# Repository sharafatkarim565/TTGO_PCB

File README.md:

# TTGO_PCB
TECHTONICS TTGO T-Call v1.3 ESP32 Wireless Communication Module for Arduino | SIM800L GPRS Module (with Antenna)

#TOP VIEW

#BOTTOM VIEW

https://github.com/sharafatkarim565/TTGO_PCB/assets/169882984/35da6a52-983e-43cd-ab66-9002d637396b

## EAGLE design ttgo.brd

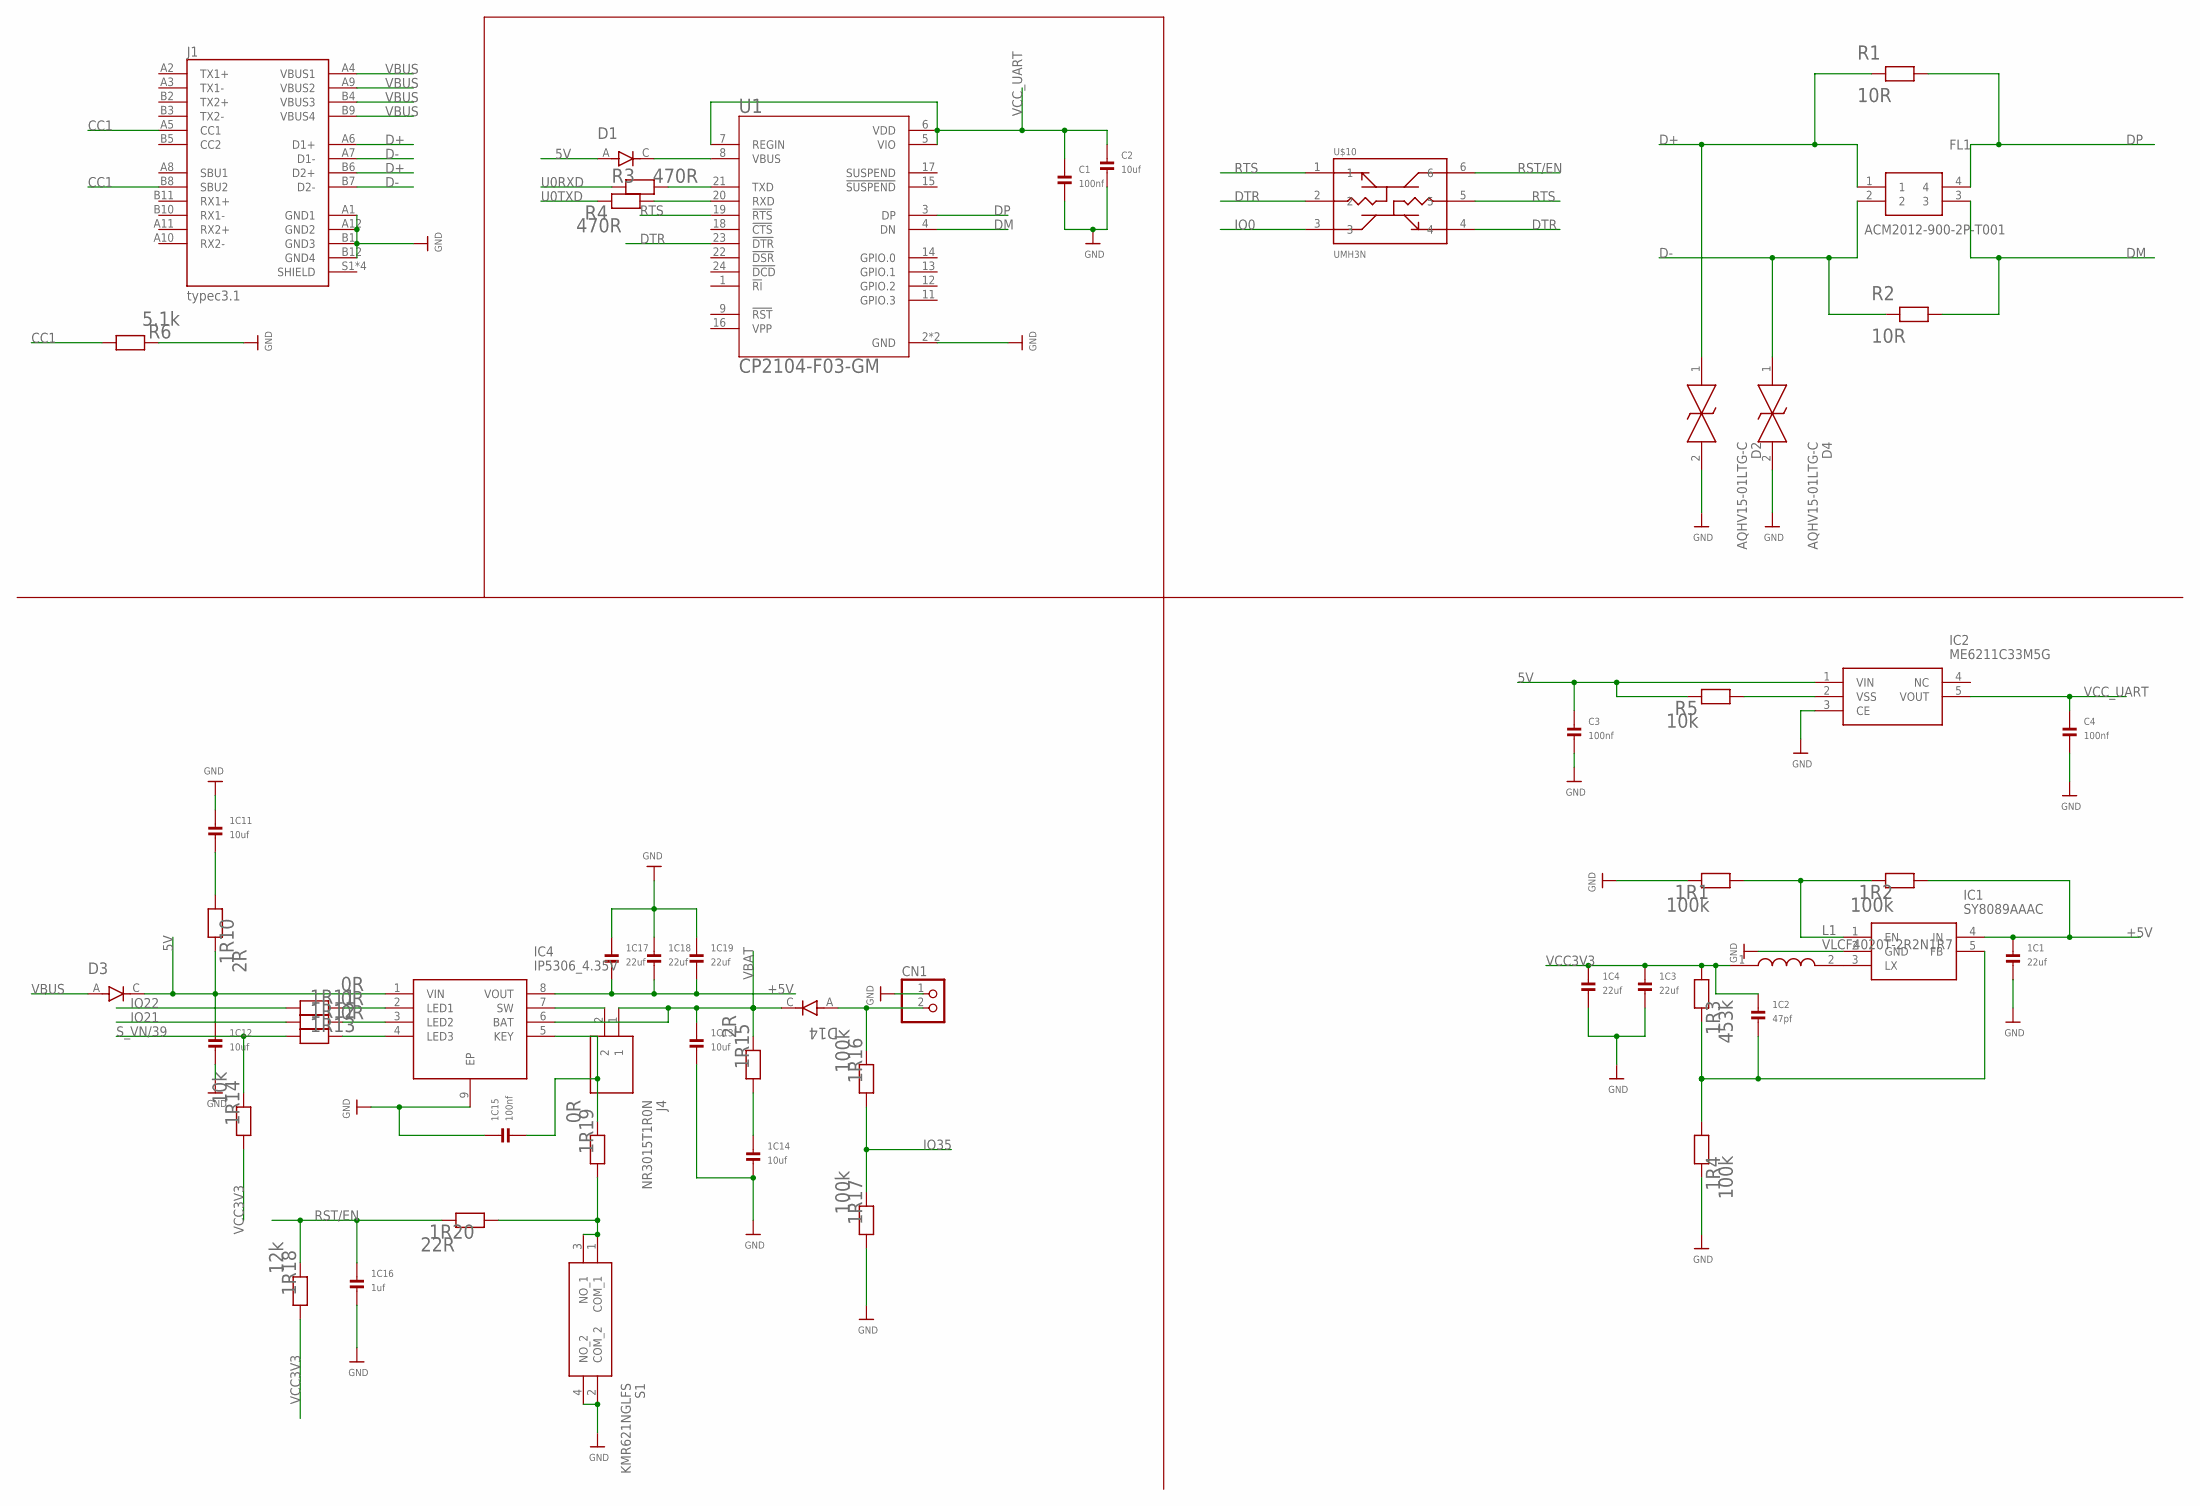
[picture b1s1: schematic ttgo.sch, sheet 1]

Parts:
1C1, 1C3, 1C4, 1C17, 1C18, 1C19: 22uf; _0402
1C2: 47pf; _0402
1C11, 1C12, 1C13, 1C14: 10uf; _0402
1C15: 100nf; _0402
1C16: 1uf; _0402
1R1, 1R2, 1R4, 1R16, 1R17: 100k; 0402
1R3: 453k; 0402
1R10, 1R15: 2R; 0402
1R11, 1R12, 1R13, 1R19: 0R; 0402
1R14: 10k; 0402
1R18: 12k; 0402
1R20: 22R; 0402
C1, C3, C4: 100nf; _0402
C2: 10uf; _0402
CN1: JST_2PINSH2; JSTSH2
D1, D3, D14: 1N4148WT; SODFL1608X70N
D2, D4: AQHV15-01LTG-C; AQHV1501LTGC
FL1: ACM2012-900-2P-T001; ACM20129002PT001
IC1: SY8089AAAC; SOT95P285X140-5N
IC2: ME6211C33M5G; SOT95P282X145-5N
IC4: IP5306_4.35V; SOIC127P600X165-9N
J1: typec3.1; MOLEX_105450-0101
J4: NR3015T1R0N
L1: VLCF4020T-2R2N1R7; VLCF4020_1
R1, R2: 10R; 0402
R3, R4: 470R; 0402
R5: 10k; 0402
R6: 5.1k; 0402
S1: KMR621NGLFS
U1: CP2104-F03-GM; QFN50P400X400X80-25N
U$10: UMH3N; SOP65P210X100-6N

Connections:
5V: 1C12.1, 1R10.1, C3.1, D1.A, D3.C, IC2.1 (VIN), IC4.1 (VIN), R5.1
+5V: 1C1.1, 1C17.2, 1C18.2, 1C19.2, 1R2.2, IC1.4 (IN), IC4.8 (VOUT); also elsewhere on the board
CC1: J1.A5 (CC1), J1.B8 (SBU2), R6.2
D+: D2.1, FL1.1, J1.A6 (D1+), J1.B6 (D2+), R1.1
D-: D4.1, FL1.2, J1.A7 (D1-), J1.B7 (D2-), R2.1
DM: FL1.3, R2.2, U1.4 (DN)
DP: FL1.4, R1.2, U1.3 (DP)
DTR: U1.23 (!DTR), U$10.2, U$10.4
GND: 1C1.2, 1C3.2, 1C4.2, 1C11.1, 1C12.2, 1C13.2, 1C14.2, 1C15.1, 1C16.2, 1C17.1, 1C18.1, 1C19.1, 1R1.1, 1R4.1, 1R17.2, C1.2, C2.2, C3.2, C4.2, CN1.1, D2.2, D4.2, IC1.2 (GND), IC2.3 (CE), IC4.9 (EP), J1.A1 (GND1), J1.A12 (GND2), J1.B1 (GND3), J1.B12 (GND4), R6.1, S1.2 (COM_2), S1.4 (NO_2), U1.2 (GND), U1.25 (GND); also elsewhere on the board
IO0: U$10.3; also elsewhere on the board
IO21: 1R12.2; also elsewhere on the board
IO22: 1R11.2; also elsewhere on the board
IO35: 1R16.2, 1R17.1; also elsewhere on the board
unnamed: D1.C, U1.8 (VBUS)
unnamed: R3.2, U1.21 (TXD)
unnamed: R4.2, U1.20 (RXD)
unnamed: IC2.2 (VSS), R5.2
unnamed: 1R1.2, 1R2.1, IC1.1 (EN)
unnamed: IC1.3 (LX), L1.2
unnamed: 1C2.2, 1R3.1, 1R4.2, IC1.5 (FB)
unnamed: 1C14.1, 1R15.2
unnamed: 1C11.2, 1R10.2
unnamed: 1R11.1, IC4.2 (LED1)
unnamed: 1C15.2, 1R19.1, IC4.5 (KEY)
unnamed: 1R12.1, IC4.3 (LED2)
unnamed: 1R16.1, CN1.2, D14.A
unnamed: 1R13.1, IC4.4 (LED3)
unnamed: IC4.7 (SW), J4.2
unnamed: 1R19.2, 1R20.2, S1.1 (COM_1), S1.3 (NO_1)
RST/EN: 1C16.1, 1R18.1, 1R20.1, U$10.6; also elsewhere on the board
RTS: U1.19 (!RTS), U$10.1, U$10.5
S_VN/39: 1R13.2, 1R14.1; also elsewhere on the board
U0RXD: R3.1; also elsewhere on the board
U0TXD: R4.1; also elsewhere on the board
VBAT: 1C13.1, 1R15.1, D14.C, IC4.6 (BAT), J4.1
VBUS: D3.A, J1.A4 (VBUS1), J1.A9 (VBUS2), J1.B4 (VBUS3), J1.B9 (VBUS4)
VCC3V3: 1C2.1, 1C3.1, 1C4.1, 1R3.2, 1R14.2, 1R18.2, L1.1; also elsewhere on the board
VCC_UART: C1.1, C2.1, C4.1, IC2.5 (VOUT), U1.5 (VIO), U1.6 (VDD), U1.7 (REGIN)

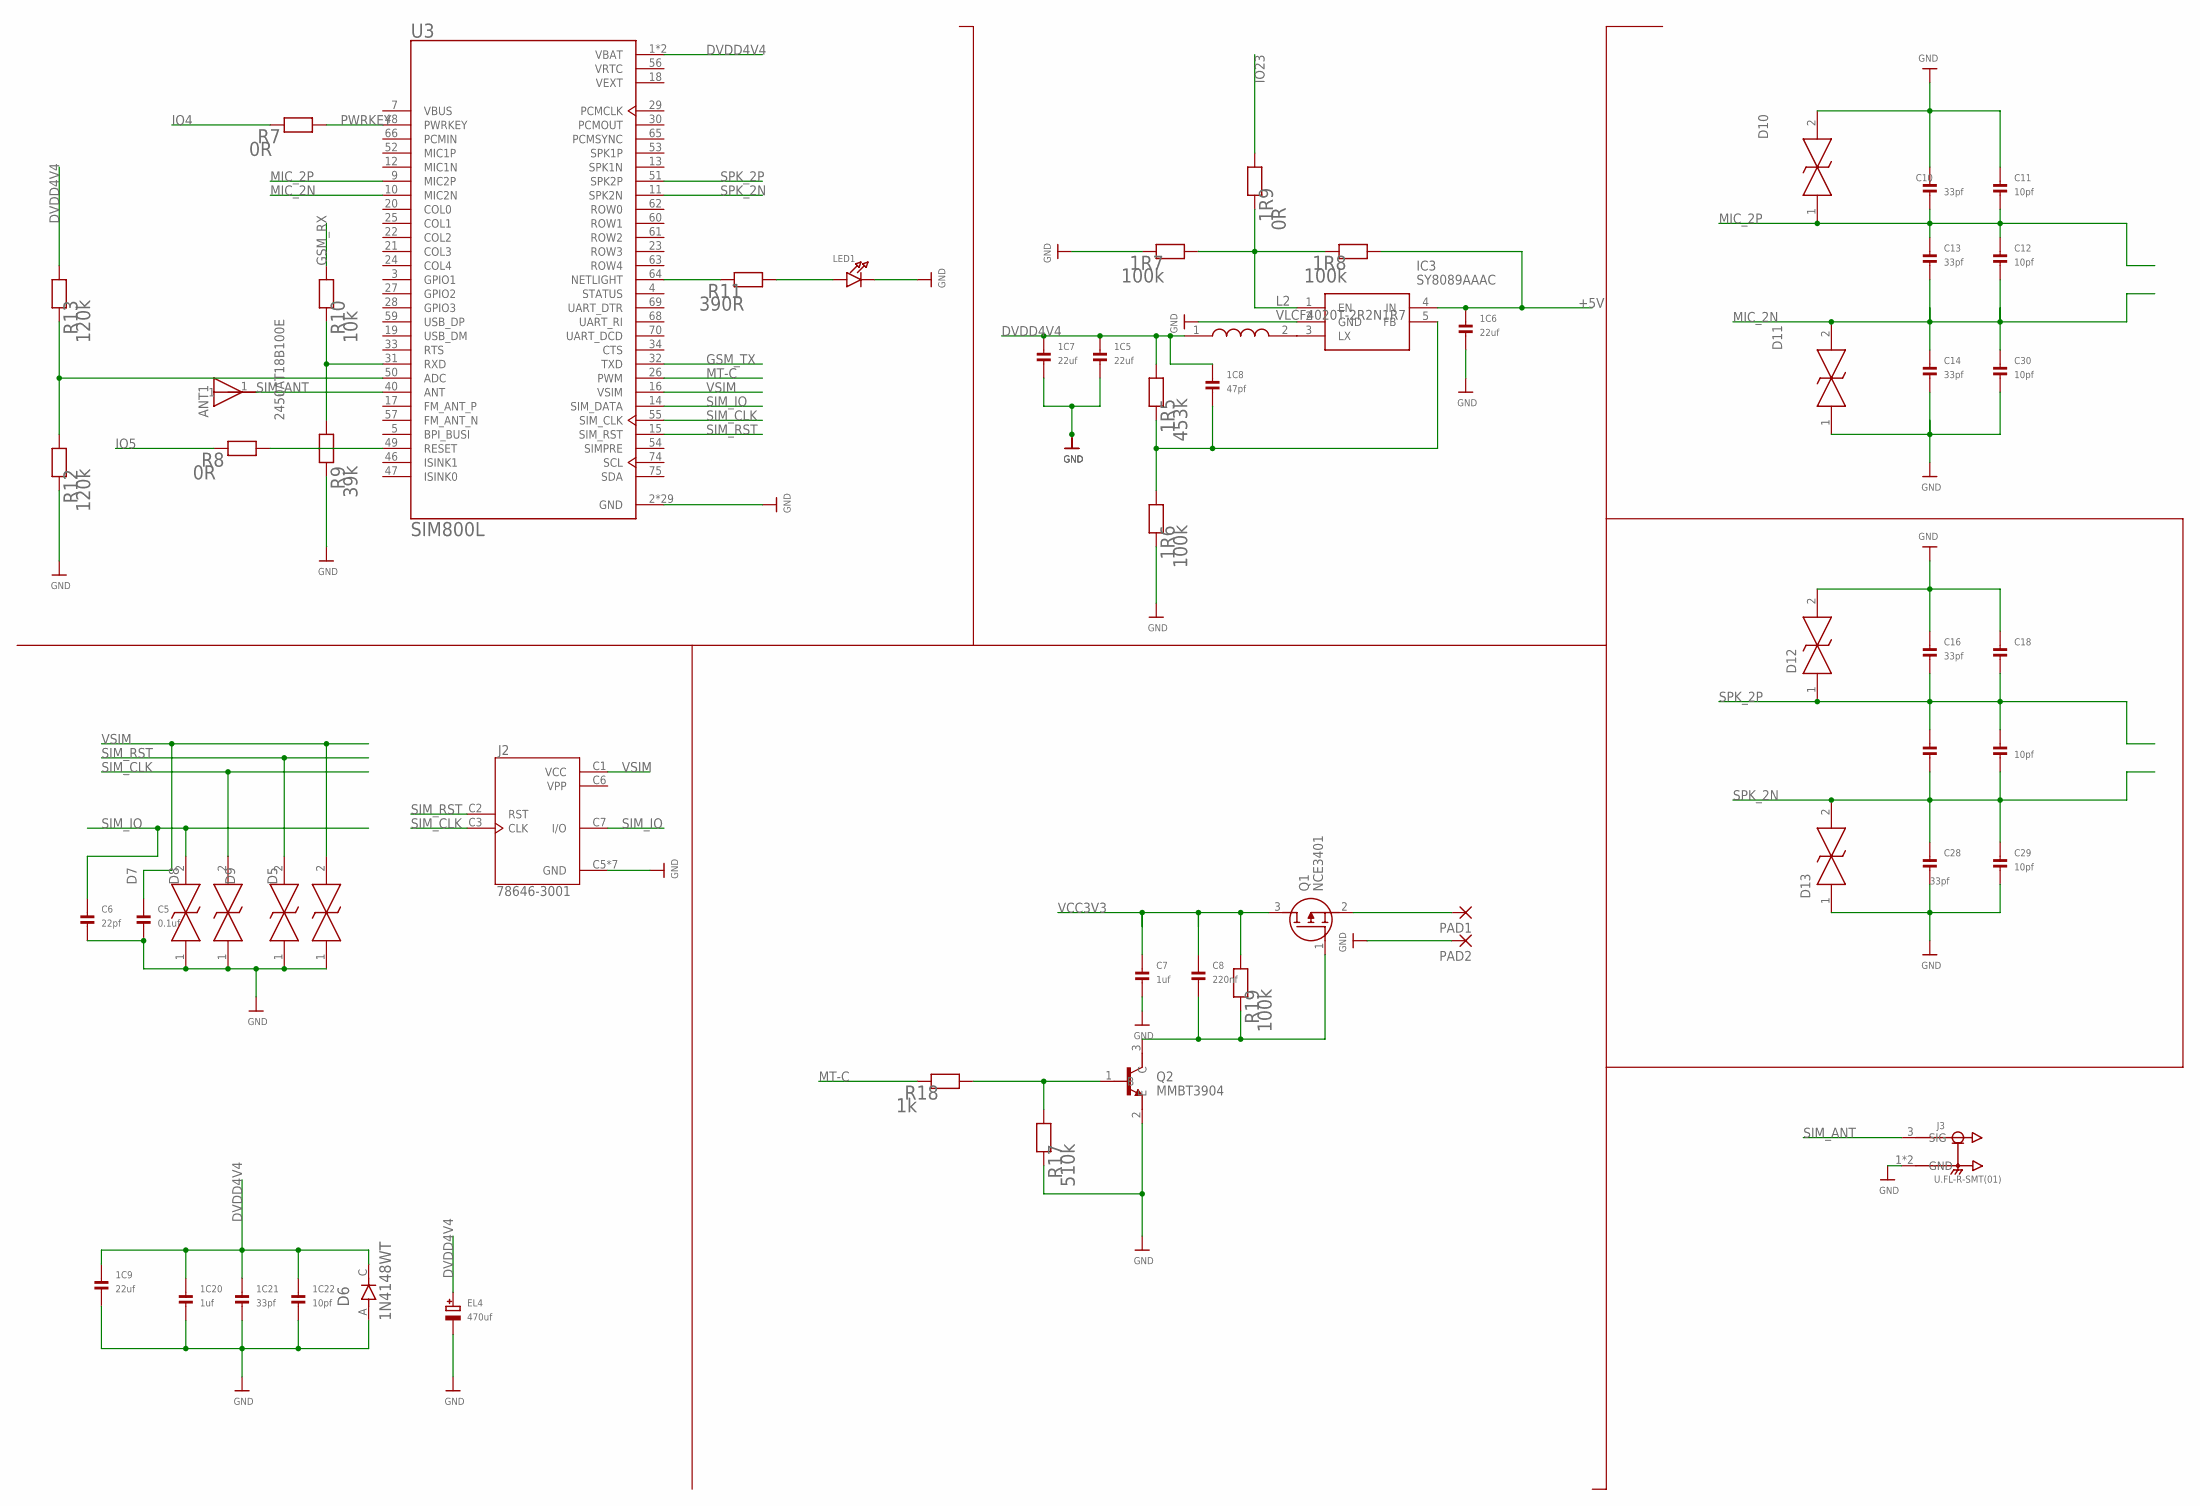
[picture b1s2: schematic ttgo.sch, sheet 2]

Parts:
1C5, 1C6, 1C7, 1C9: 22uf; _0402
1C8: 47pf; _0402
1C20: 1uf; _0402
1C21: 33pf; _0402
1C22: 10pf; _0402
1R5: 453k; 0402
1R6, 1R7, 1R8: 100k; 0402
1R9: 0R; 0402
ANT1: 2450AT18B100E; ANT_2450AT18B100E
C5: 0.1uf; _0402
C6: 22pf; _0402
C7: 1uf; _0402
C8: 220nf; _0402
C10, C13, C14, C16, C26, C28: 33pf; _0402
C11, C12, C18, C20, C29, C30: 10pf; _0402
D5, D7, D8, D9, D10, D11, D12, D13: AQHV15-01LTG-C; AQHV1501LTGC
D6: 1N4148WT; SODFL1608X70N
EL4: 470uf; EIA6032-28/C-R
IC3: SY8089AAAC; SOT95P285X140-5N
J2: 78646-3001; MOLEX_78646-3001
J3: U.FL-R-SMT(01); HRS_U.FL-R-SMT(01)
L2: VLCF4020T-2R2N1R7; VLCF4020_1
LED1: LED0603_NOOUTLINE; CHIPLED_0603_NOOUTLINE
PAD1, PAD2: SMD2; SMD1,27-2,54
Q1: NCE3401; SOT95P240X115-3N
Q2: MMBT3904; SOT95P240X120-3N
R7, R8: 0R; 0402
R9: 39k; 0402
R10: 10k; 0402
R11: 390R; 0402
R12, R13: 120k; 0402
R17: 510k; 0402
R18: 1k; 0402
R19: 100k; 0402
U3: SIM800L; MODULE_SIM800L

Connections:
+5V: 1C6.1, 1R8.2, IC3.4 (IN); also elsewhere on the board
DVDD4V4: 1C5.1, 1C7.1, 1C8.1, 1C9.1, 1C20.1, 1C21.1, 1C22.1, 1R5.2, D6.C, EL4.+, L2.1, R13.2, U3.1 (VBAT), U3.42 (VBAT)
GND: 1C5.2, 1C6.2, 1C7.2, 1C9.2, 1C20.2, 1C21.2, 1C22.2, 1R6.1, 1R7.1, C5.2, C6.2, C7.2, C10.1, C11.1, C14.2, C16.1, C18.1, C28.2, C29.2, C30.2, D5.1, D6.A, D7.1, D8.1, D9.1, D10.2, D11.1, D12.2, D13.1, EL4.-, IC3.2 (GND), J2.C5 (GND), J2.G1 (GND), J2.G2 (GND), J2.G3 (GND), J2.G4 (GND), J2.G5 (GND), J2.G6 (GND), J3.1 (GND), J3.2 (GND), LED1.C, PAD2.1, Q2.2 (E), R9.1, R12.1, R17.1, U3.2 (GND), U3.6 (GND), U3.8 (GND), U3.35 (GND), U3.37 (GND), U3.38 (GND), U3.39 (GND), U3.41 (GND), U3.43 (GND), U3.44 (GND), U3.45 (GND), U3.58 (GND), U3.67 (GND), U3.71 (GND), U3.72 (GND), U3.73 (GND), U3.76 (GND), U3.77 (GND), U3.78 (GND), U3.79 (GND), U3.80 (GND), U3.81 (GND), U3.82 (GND), U3.83 (GND), U3.84 (GND), U3.85 (GND), U3.86 (GND), U3.87 (GND), U3.88 (GND); also elsewhere on the board
GSM_RX: R10.2; also elsewhere on the board
GSM_TX: U3.32 (TXD); also elsewhere on the board
IO4: R7.1; also elsewhere on the board
IO5: R8.1; also elsewhere on the board
IO23: 1R9.2; also elsewhere on the board
MIC_2N: C12.2, C13.2, C14.1, C30.1, D11.2, U3.10 (MIC2N); also elsewhere on the board
MIC_2P: C10.2, C11.2, C12.1, C13.1, D10.1, U3.9 (MIC2P); also elsewhere on the board
MT-C: R18.1, U3.26 (PWM)
unnamed: 1R7.2, 1R8.1, 1R9.1, IC3.1 (EN)
unnamed: R12.2, R13.1, U3.50 (ADC)
unnamed: IC3.3 (LX), L2.2
unnamed: R11.1, U3.64 (NETLIGHT)
unnamed: 1C8.2, 1R5.1, 1R6.2, IC3.5 (FB)
unnamed: Q2.1 (B), R17.2, R18.2
unnamed: PAD1.1, Q1.2 (S)
unnamed: R9.2, R10.1, U3.31 (RXD)
unnamed: R8.2, U3.49 (RESET)
unnamed: C8.2, Q1.1 (G), Q2.3 (C), R19.1
unnamed: LED1.A, R11.2
PWRKEY: R7.2, U3.48 (PWRKEY)
SIM_ANT: ANT1.1, J3.3 (SIG), U3.40 (ANT)
SIM_CLK: D8.2, J2.C3 (CLK), U3.55 (SIM_CLK)
SIM_IO: C6.1, D7.2, J2.C7 (I/O), U3.14 (SIM_DATA)
SIM_RST: D9.2, J2.C2 (RST), U3.15 (SIM_RST)
SPK_2N: C20.2, C26.2, C28.1, C29.1, D13.2, U3.11 (SPK2N); also elsewhere on the board
SPK_2P: C16.2, C18.2, C20.1, C26.1, D12.1, U3.51 (SPK2P); also elsewhere on the board
VCC3V3: C7.1, C8.1, Q1.3 (D), R19.2; also elsewhere on the board
VEXT: U3.18 (VEXT)
VPP: J2.C6 (VPP)
VRTC: U3.56 (VRTC)
VSIM: C5.1, D5.2, J2.C1 (VCC), U3.16 (VSIM)

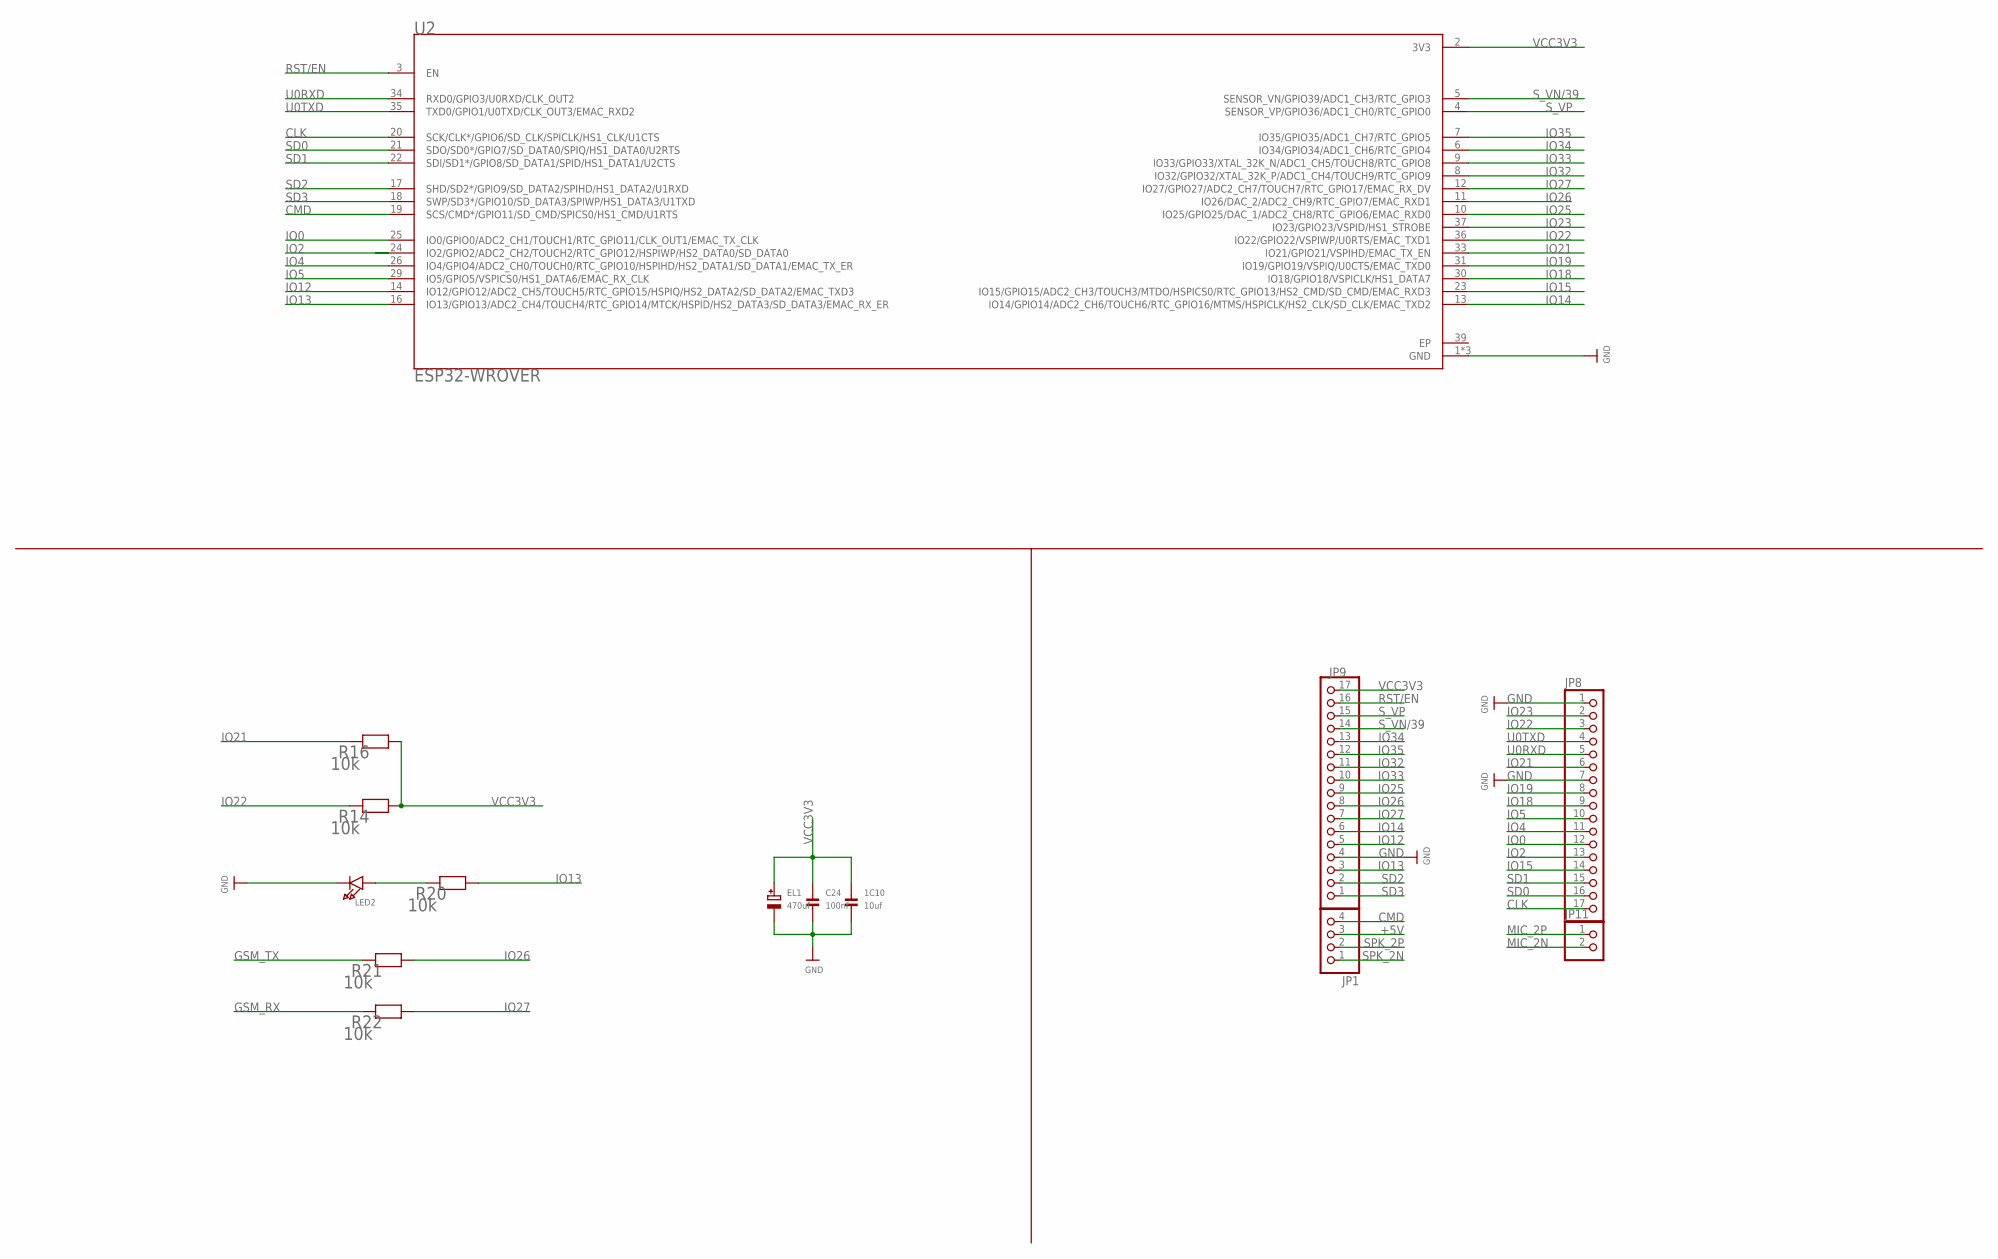
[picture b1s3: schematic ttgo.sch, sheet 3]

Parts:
1C10: 10uf; _0402
C24: 100nf; _0402
EL1: 470uf; EIA6032-28/C-R
JP1: HEADER-1X4ROUND; 1X04_ROUND
JP8, JP9: HEADER-1X17; 1X17_ROUND70
JP11: HEADER-1X2ROUND; 1X02_ROUND
LED2: LED0603_NOOUTLINE; CHIPLED_0603_NOOUTLINE
R14, R16, R20, R21, R22: 10k; 0402
U2: ESP32-WROVER; XCVR_ESP32-WROVER

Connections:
+5V: JP1.3; also elsewhere on the board
CLK: JP8.17, U2.20 (SCK/CLK*/GPIO6/SD_CLK/SPICLK/HS1_CLK/U1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)
CMD: JP1.4, U2.19 (SCS/CMD*/GPIO11/SD_CMD/SPICS0/HS1_CMD/U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)
EP: U2.39 (EP)
GND: 1C10.2, C24.2, EL1.-, JP8.1, JP8.7, JP9.4, LED2.C, U2.1 (GND), U2.15 (GND), U2.38 (GND); also elsewhere on the board
GSM_RX: R22.1; also elsewhere on the board
GSM_TX: R21.1; also elsewhere on the board
IO0: JP8.12, U2.25 (IO0/GPIO0/ADC2_CH1/TOUCH1/RTC_GPIO11/CL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); also elsewhere on the board
IO2: JP8.13, U2.24 (IO2/GPIO2/ADC2_CH2/TOUCH2/RTC_GPIO12/HS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)
IO4: JP8.11, U2.26 (IO4/GPIO4/ADC2_CH0/TOUCH0/RTC_GPIO10/HS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); also elsewhere on the board
IO5: JP8.10, U2.29 (IO5/GPIO5/VSPICS0/HS1_DATA6/EMAC_RX_CLK); also elsewhere on the board
IO12: JP9.5, U2.14 (IO12/GPIO12/ADC2_CH5/TOUCH5/RTC_GPIO15/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)
IO13: JP9.3, R20.2, U2.16 (IO13/GPIO13/ADC2_CH4/TOUCH4/RTC_GPIO14/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)
IO14: JP9.6, U2.13 (IO14/GPIO14/ADC2_CH6/TOUCH6/RTC_GPIO16/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)
IO15: JP8.14, U2.23 (IO15/GPIO15/ADC2_CH3/TOUCH3/MTDO/HSPICS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)
IO18: JP8.9, U2.30 (IO18/GPIO18/VSPICLK/HS1_DATA7)
IO19: JP8.8, U2.31 (IO19/GPIO19/VSPIQ/U0CTS/EMAC_TXD0)
IO21: JP8.6, R16.1, U2.33 (IO21/GPIO21/VSPIHD/EMAC_TX_EN); also elsewhere on the board
IO22: JP8.3, R14.1, U2.36 (IO22/GPIO22/VSPIWP/U0RTS/EMAC_TXD1); also elsewhere on the board
IO23: JP8.2, U2.37 (IO23/GPIO23/VSPID/HS1_STROBE); also elsewhere on the board
IO25: JP9.9, U2.10 (IO25/GPIO25/DAC_1/ADC2_CH8/RTC_GPIO6/EM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)
IO26: JP9.8, R21.2, U2.11 (IO26/DAC_2/ADC2_CH9/RTC_GPIO7/EMAC_RXD1)
IO27: JP9.7, R22.2, U2.12 (IO27/GPIO27/ADC2_CH7/TOUCH7/RTC_GPIO17/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)
IO32: JP9.11, U2.8 (IO32/GPIO32/XTAL_32K_P/ADC1_CH4/TOUCH9/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)
IO33: JP9.10, U2.9 (IO33/GPIO33/XTAL_32K_N/ADC1_CH5/TOUCH8/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)
IO34: JP9.13, U2.6 (IO34/GPIO34/ADC1_CH6/RTC_GPIO4)
IO35: JP9.12, U2.7 (IO35/GPIO35/ADC1_CH7/RTC_GPIO5); also elsewhere on the board
MIC_2N: JP11.2; also elsewhere on the board
MIC_2P: JP11.1; also elsewhere on the board
unnamed: LED2.A, R20.1
RST/EN: JP9.16, U2.3 (EN); also elsewhere on the board
SD0: JP8.16, U2.21 (SDO/SD0*/GPIO7/SD_DATA0/SPIQ/HS1_DATA0/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)
SD1: JP8.15, U2.22 (SDI/SD1*/GPIO8/SD_DATA1/SPID/HS1_DATA1/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)
SD2: JP9.2, U2.17 (SHD/SD2*/GPIO9/SD_DATA2/SPIHD/HS1_DATA2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)
SD3: JP9.1, U2.18 (SWP/SD3*/GPIO10/SD_DATA3/SPIWP/HS1_DATA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)
SPK_2N: JP1.1; also elsewhere on the board
SPK_2P: JP1.2; also elsewhere on the board
S_VN/39: JP9.14, U2.5 (SENSOR_VN/GPIO39/ADC1_CH3/RTC_GPIO3); also elsewhere on the board
S_VP: JP9.15, U2.4 (SENSOR_VP/GPIO36/ADC1_CH0/RTC_GPIO0)
U0RXD: JP8.5, U2.34 (RXD0/GPIO3/U0RXD/CLK_OUT2); also elsewhere on the board
U0TXD: JP8.4, U2.35 (TXD0/GPIO1/U0TXD/CLK_OUT3/EMAC_RXD2); also elsewhere on the board
VCC3V3: 1C10.1, C24.1, EL1.+, JP9.17, R14.2, R16.2, U2.2 (3V3); also elsewhere on the board

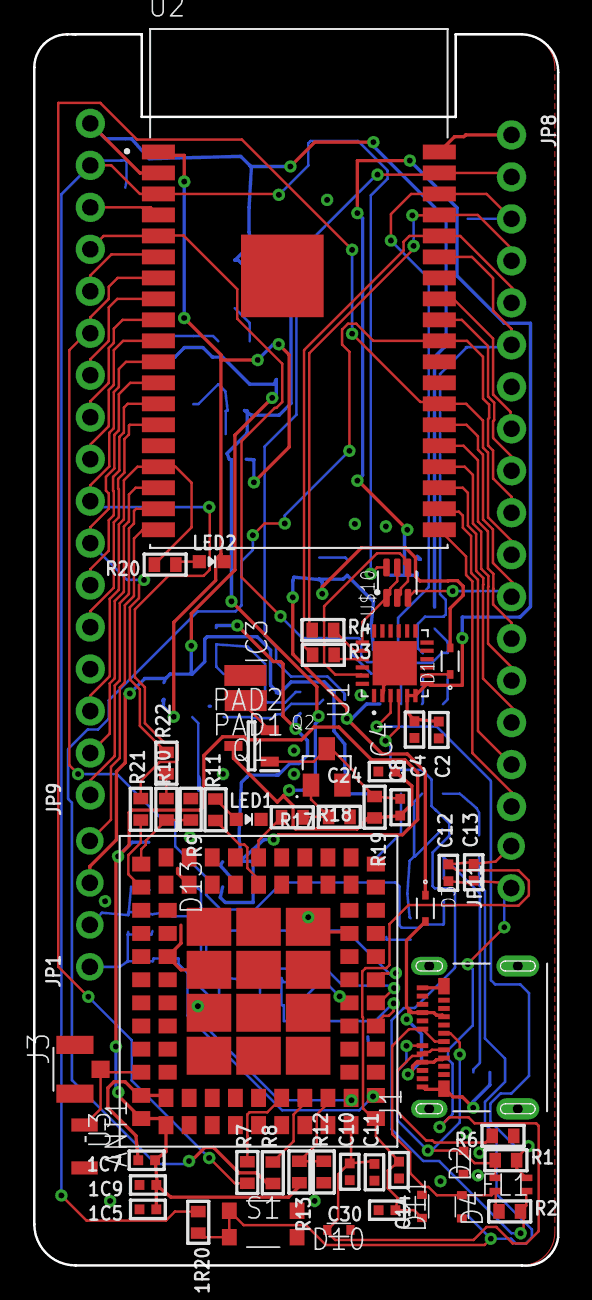
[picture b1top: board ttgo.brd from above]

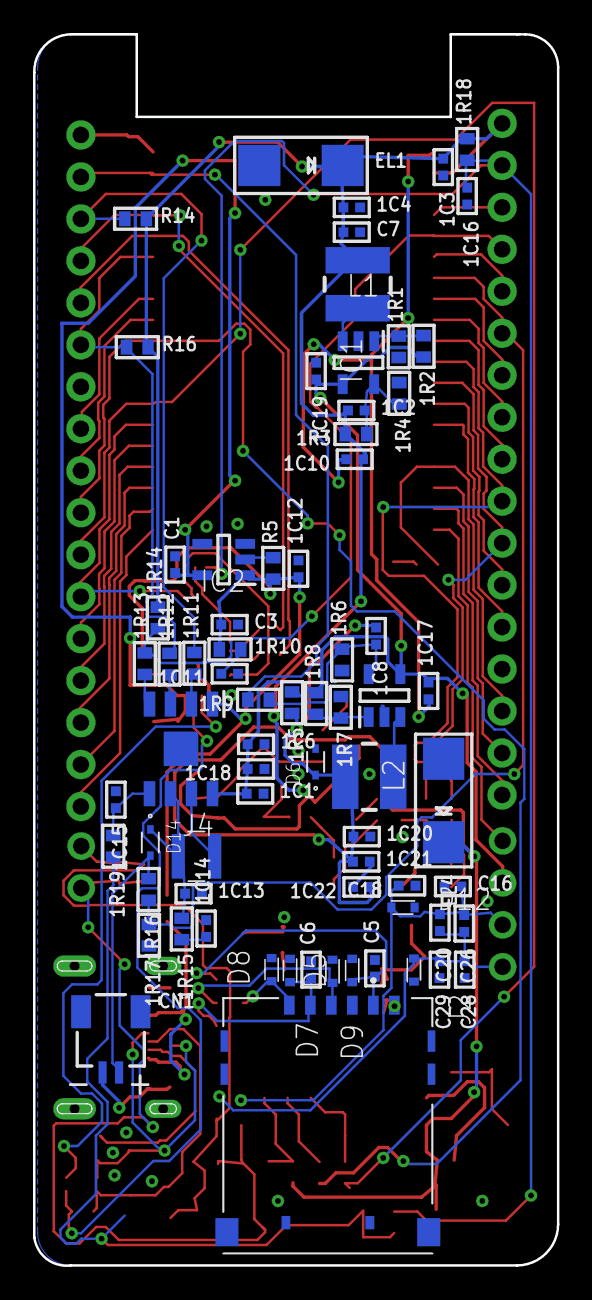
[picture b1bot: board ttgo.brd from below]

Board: 2 copper layers, 31.7 x 74.5 mm, 128 parts (71 on the bottom side), 87 nets.

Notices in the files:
parts and their libraries:
microbuilder: This work is placed in the public domain, and may be freely used for commercial and non-commercial work with the following conditions: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
